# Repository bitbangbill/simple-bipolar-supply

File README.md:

# Simple Bipolar Supply

The simple bipolar supply is a USB-C powered dual channel (positive and negative) power supply. The module is a drop in system for projects requiring a bipolar suppy. The project is designed to be a series of building blocks a tailored supply for any application.

## Gallery

*Revision B of the charge-pump variant rendered in KiCad*

## Features

### Generic
* USB-C powered.
* Dual channel +/- with respect to ground.
* Filtered output.
* Pin pitch designed for breadboard compatibility.
* Pi filtered output.

## Status : Prototype phase
### Issues
* None so far! 🤞

### In The Works
* Initial proof of concept for the charge pump variant of the suppy.
* PCB and parts order on the way for testing RevA.
* Regulated and adjustable output stage for the lower voltage version.

### Roadmap
The long term plan is to develop multiple building blocks for two primary variants of the power supply. The building blocks and whole system are outlined in the system block diagram. Only the first two blocks are implemented in the first revision. Each block in the diagram between USB-C and output can be added and removed as necesary.

*Block diagram convering the project roadmap*

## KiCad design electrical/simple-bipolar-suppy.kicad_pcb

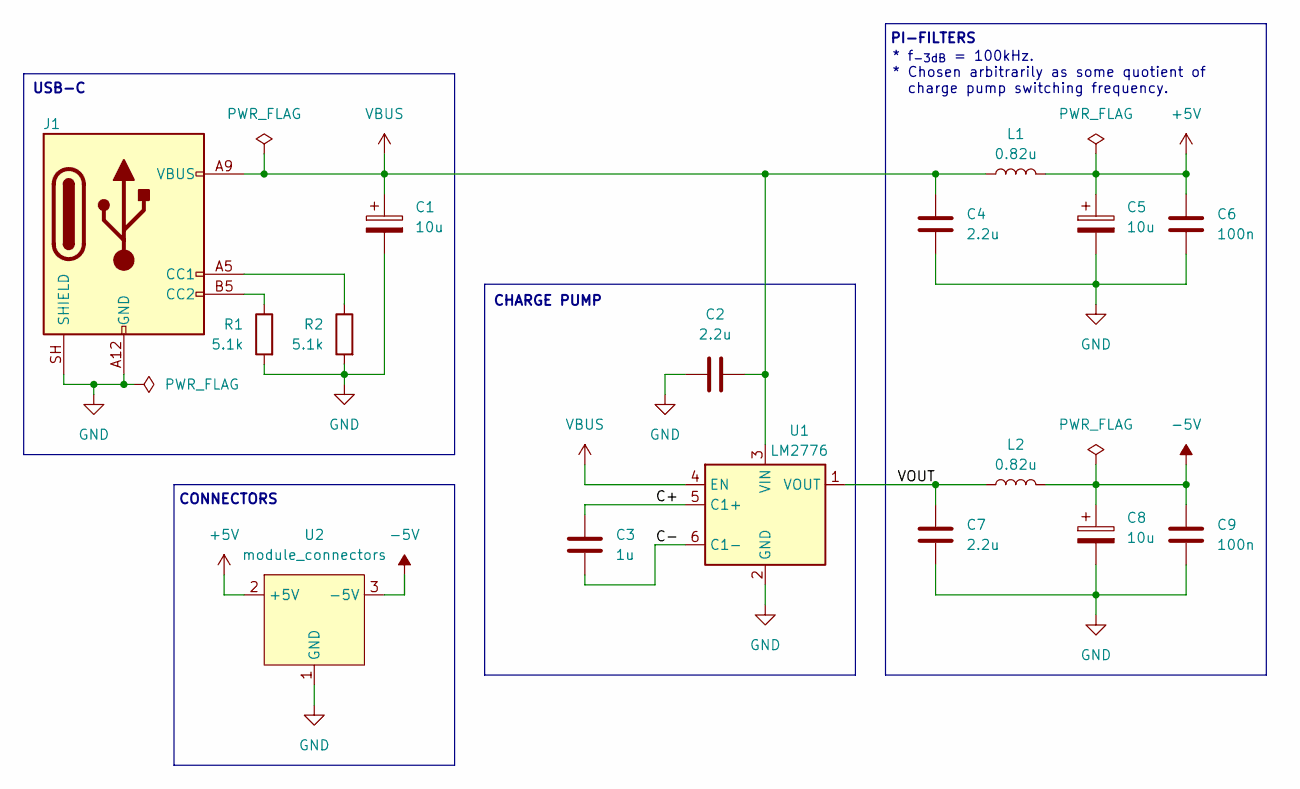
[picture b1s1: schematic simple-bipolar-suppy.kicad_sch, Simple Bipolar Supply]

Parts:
C1, C5, C8: 10u; CP_EIA-3528-12_Kemet-T
C2, C4, C7: 2.2u; C_0805_2012Metric
C3: 1u; C_0805_2012Metric
C6, C9: 100n; C_0805_2012Metric
J1: USB_C_Receptacle_PowerOnly_6P; USB_C_Receptacle_GCT_USB4135-GF-A_6P_TopMnt_Horizontal
L1, L2: 0.82u; SRP4020
R1, R2: 5.1k; R_0805_2012Metric
U1: LM2776; SOT-23-6
U2: module_connectors; module-footprint

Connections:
+5V: C5.1, C6.1, L1.2, U2.2 (+5V)
-5V: C8.1, C9.1, L2.2, U2.3 (-5V)
/C+: C3.2, U1.5 (C1+)
/C-: C3.1, U1.6 (C1-)
/VOUT: C7.1, L2.1, U1.1 (VOUT)
GND: C1.2, C2.1, C4.2, C5.2, C6.2, C7.2, C8.2, C9.2, J1.A12 (GND), J1.B12 (GND), J1.SH (SHIELD), R1.2, R2.2, U1.2 (GND), U2.1 (GND)
unnamed: J1.A5 (CC1), R2.1
unnamed: J1.B5 (CC2), R1.1
VBUS: C1.1, C2.2, C4.1, J1.A9 (VBUS), J1.B9 (VBUS), L1.1, U1.3 (VIN), U1.4 (EN)

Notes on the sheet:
* f_{-3dB} = 100kHz. * Chosen arbitrarily as some quotient of charge pump switching frequency.
PI-FILTERS
CONNECTORS
CHARGE PUMP
USB-C

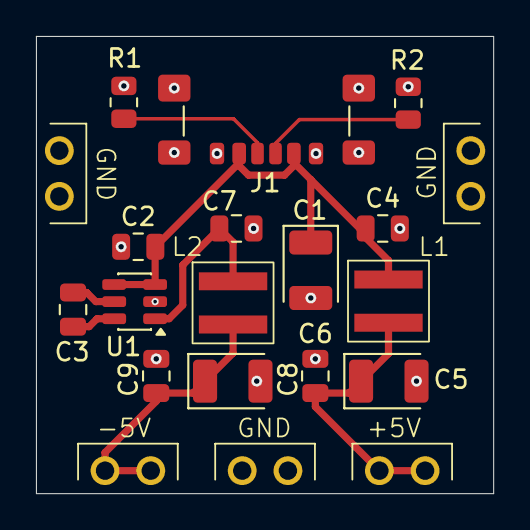
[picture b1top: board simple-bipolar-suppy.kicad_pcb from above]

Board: 2 copper layers, 25.4 x 25.4 mm, 16 parts (0 on the bottom side), 9 nets.
